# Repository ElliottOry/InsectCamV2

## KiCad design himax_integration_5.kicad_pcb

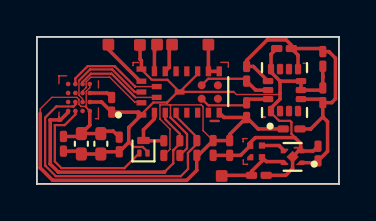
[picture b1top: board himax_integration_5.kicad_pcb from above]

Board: 2 copper layers, 16.8 x 8.2 mm, 29 parts (0 on the bottom side), 19 nets.

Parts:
C1, C10: 0.1u; C_0201_0603Metric_Pad0.64x0.40mm_HandSolder
C2: 2.2u; C_0201_0603Metric_Pad0.64x0.40mm_HandSolder
C3: 10n; C_0201_0603Metric_Pad0.64x0.40mm_HandSolder
C4, C5, C6: 0.1uF; C_0201_0603Metric_Pad0.64x0.40mm_HandSolder
C7, C8: 10uF; C_0402_1005Metric_Pad0.74x0.62mm_HandSolder
C9, C12: 1.0 uF; C_0201_0603Metric_Pad0.64x0.40mm_HandSolder
C11: 4.7u; C_0201_0603Metric_Pad0.64x0.40mm_HandSolder
HM01B1: camerah
J1: VBat; ExternalPad_FP
J2: GND Pad; ExternalPad_FP
J3: SWDCLK Pad; ExternalPad_FP
J4: SWDIO Pad; ExternalPad_FP
J5: RST Pad; ExternalPad_FP
J6: Antenna Pad; ExternalPad_FP
Q2: Q_NPN; SOT-883_1
R1, R2, R3, R4, R5: 4.7k; R_0201_0603Metric_Pad0.64x0.40mm_HandSolder
U1: ICM-42688-P; PQFN50P300X250X97-14N
U2: MAG_Switch; RR122
U3: ES2832AA2; XCVR_ES2832AA2_NO_ANTENNA
VR1: TCR3UM33A; VREG_TCR3UM33A

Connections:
3.2V: C1.1, C2.1, C3.1, C4.1, C5.1, C7.1, C8.1, C10.1, C11.1, C12.2, HM01B1.D1 (AVDD), HM01B1.D4 (IOVDD), R1.1, R2.1, R3.1, R4.1, R5.1, U1.5 (VDDIO), U1.8 (VDD), U1.12 (AP_CS), U3.8 (VCC_NRF), VR1.1 (VOUT)
Antenna: J6.1 (Pin_1_1), U3.11 (OUT_ANT), U3.12 (OUT_MOD)
D0: HM01B1.B4 (D0), U3.25 (P0.20_TRACECLK)
GND: C1.2, C2.2, C3.2, C4.2, C5.2, C6.2, C7.2, C8.2, C9.2, C10.2, C11.2, C12.1, HM01B1.D2 (GND), J2.1 (Pin_1_1), Q2.E, U1.1 (AP_SDO/AP_AD0), U1.6 (GND), U1.7 (RESV_7), U1.11 (RESV_11), U2.4 (GND), U3.1 (GND), U3.13 (GND), U3.18 (GND), U3.26 (GND), VR1.2 (GND)
HSYNC: Q2.C, R3.2, U3.2 (P0.06)
I2C0/SCL: R5.2, U1.13 (AP_SCL/AP_SCLK), U3.24 (P0.28_AIN4)
I2C0/SDA: R4.2, U1.14 (AP_SDA/AP_SDIO/AP_SDI), U3.23 (P0.02_AIN0)
I2C1/SCL: HM01B1.B2 (SCL), R2.2, U3.4 (P0.00_XL1)
I2C1/SDA: HM01B1.A1 (SDA), R1.2, U3.3 (P0.05_AIN3)
MCLK: HM01B1.C4 (MCLK), U3.22 (P0.18_TRACEDATA(0))
unnamed: C6.1, HM01B1.D3 (DVDD)
unnamed: HM01B1.B1 (LVLD), Q2.B
unnamed: C9.1, J1.1 (Pin_1_1), U2.2 (VIN), VR1.4 (VIN)
unnamed: U2.3 (VOUT), VR1.3 (CONTROL)
PCLKO: HM01B1.C3 (PCLKO), U3.21 (P0.07)
Reset: J5.1 (Pin_1_1), U3.19 (P0.21_RESET)
SWDCLK: J3.1 (Pin_1_1), U3.16 (SWDCLK)
SWDIO: J4.1 (Pin_1_1), U3.17 (SWDIO)
VSYNC: HM01B1.C2 (FVLD), U3.20 (P0.08)
